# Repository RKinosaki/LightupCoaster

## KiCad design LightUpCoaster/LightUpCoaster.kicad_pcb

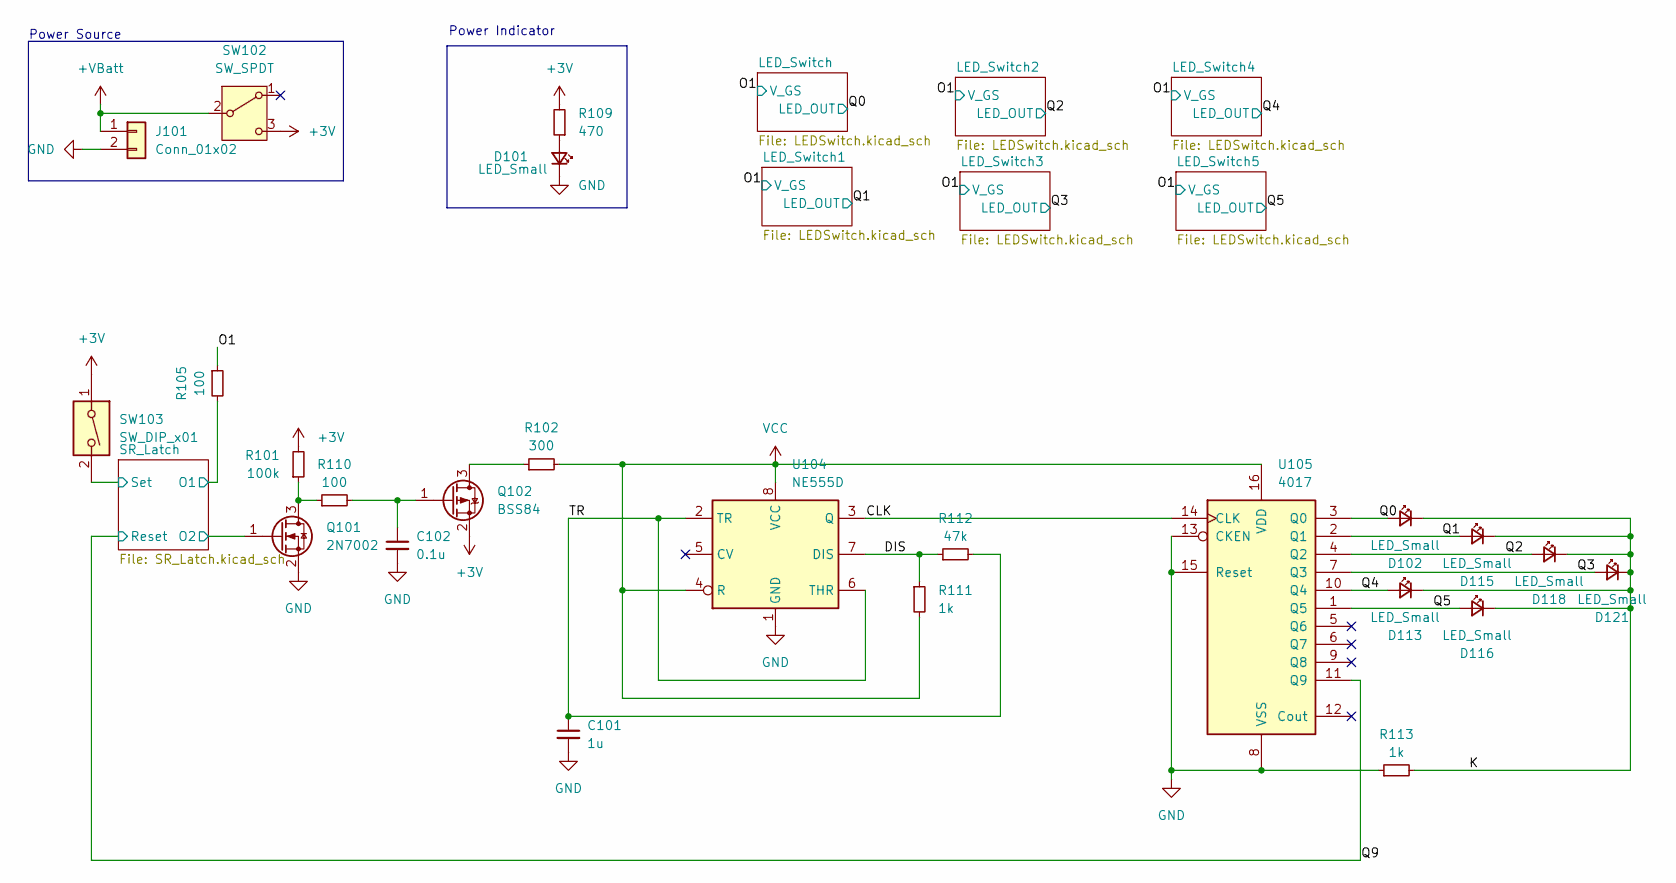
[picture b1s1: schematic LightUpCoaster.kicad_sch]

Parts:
C101: 1u; C_0402_1005Metric
C102: 0.1u; C_0402_1005Metric
D101, D102, D113, D115, D116, D118, D121: LED_Small; LED_0402_1005Metric
J101: Conn_01x02; PinHeader_1x02_P2.54mm_Vertical
Q101: 2N7002; SOT-23
Q102: BSS84; SOT-23
R101: 100k; R_0402_1005Metric
R102: 300; R_0402_1005Metric
R105, R110: 100; R_0402_1005Metric
R109: 470; R_0402_1005Metric
R111, R113: 1k; R_0402_1005Metric
R112: 47k; R_0402_1005Metric
SW102: SW_SPDT; PinHeader_1x03_P2.54mm_Vertical
SW103: SW_DIP_x01; SW_Push_1P1T_NO_E-Switch_TL3301NxxxxxG
U104: NE555D; SOIC-8_3.9x4.9mm_P1.27mm
U105: 4017; SOP-16_3.9x9.9mm_P1.27mm

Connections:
+3V: Q102.2 (S), R101.2, R109.2, SW102.3 (C), SW103.1; also elsewhere on the board
+VBatt: J101.1, SW102.2 (B)
/CLK: U104.3 (Q), U105.14 (CLK)
/DIS: R111.1, R112.1, U104.7 (DIS)
/K: D102.1 (K), D113.1 (K), D115.1 (K), D116.1 (K), D118.1 (K), D121.1 (K), R113.2
/O1: R105.1; also elsewhere on the board
/Q0: D102.2 (A), U105.3 (Q0); also elsewhere on the board
/Q1: D115.2 (A), U105.2 (Q1); also elsewhere on the board
/Q2: D118.2 (A), U105.4 (Q2); also elsewhere on the board
/Q3: D121.2 (A), U105.7 (Q3); also elsewhere on the board
/Q4: D113.2 (A), U105.10 (Q4); also elsewhere on the board
/Q5: D116.2 (A), U105.1 (Q5); also elsewhere on the board
/Q9: U105.11 (Q9); also elsewhere on the board
/SR_Latch/O1: R105.2; also elsewhere on the board
/SR_Latch/O2: Q101.1 (G); also elsewhere on the board
/SR_Latch/Set: SW103.2; also elsewhere on the board
/TR: C101.1, R112.2, U104.2 (TR), U104.6 (THR)
GND: C101.2, C102.2, D101.1 (K), J101.2, Q101.2 (S), R113.1, U104.1 (GND), U105.8 (VSS), U105.13 (CKEN), U105.15 (Reset); also elsewhere on the board
unnamed: D101.2 (A), R109.1
unnamed: Q101.3 (D), R101.1, R110.1
unnamed: Q102.3 (D), R102.1
unnamed: C102.1, Q102.1 (G), R110.2
VCC: R102.2, R111.2, U104.4 (R), U104.8 (VCC), U105.16 (VDD)

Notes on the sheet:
Power Source
Power Indicator

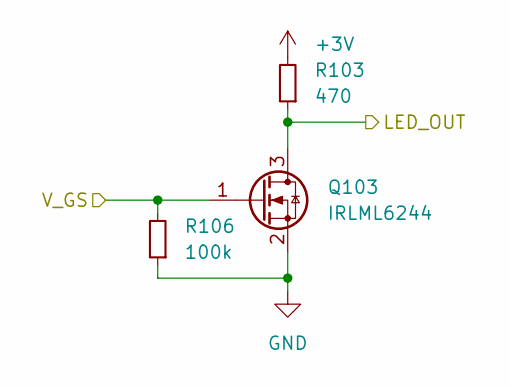
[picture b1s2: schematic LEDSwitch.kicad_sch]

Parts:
Q103: IRLML6244; SOT-23
R103: 470; R_0402_1005Metric
R106: 100k; R_0402_1005Metric

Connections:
+3V: R103.2; also elsewhere on the board
/O1: Q103.1 (G), R106.2; also elsewhere on the board
/Q0: Q103.3 (D), R103.1; also elsewhere on the board
GND: Q103.2 (S), R106.1; also elsewhere on the board

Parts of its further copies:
Q401, Q402, Q403, Q501, Q601: IRLML6244; SOT-23
R401, R403, R405, R501, R601: 100k; R_0402_1005Metric
R402, R404, R406, R502, R602: 470; R_0402_1005Metric

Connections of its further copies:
+3V: R402.2, R404.2, R406.2, R502.2, R602.2; also elsewhere on the board
/O1: Q401.1 (G), Q402.1 (G), Q403.1 (G), Q501.1 (G), Q601.1 (G), R401.2, R403.2, R405.2, R501.2, R601.2; also elsewhere on the board
/Q1: Q401.3 (D), R402.1; also elsewhere on the board
/Q2: Q403.3 (D), R406.1; also elsewhere on the board
/Q3: Q601.3 (D), R602.1; also elsewhere on the board
/Q4: Q402.3 (D), R404.1; also elsewhere on the board
/Q5: Q501.3 (D), R502.1; also elsewhere on the board
GND: Q401.2 (S), Q402.2 (S), Q403.2 (S), Q501.2 (S), Q601.2 (S), R401.1, R403.1, R405.1, R501.1, R601.1; also elsewhere on the board

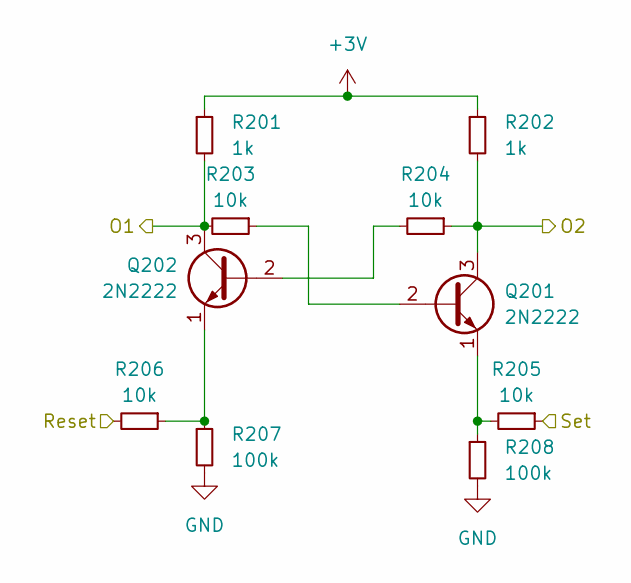
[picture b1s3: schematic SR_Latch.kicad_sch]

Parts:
Q201: 2N2222; TO-92
Q202: 2N2222; SOT-23
R201, R202: 1k; R_0402_1005Metric
R203, R204, R205, R206: 10k; R_0402_1005Metric
R207, R208: 100k; R_0402_1005Metric

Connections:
+3V: R201.1, R202.1; also elsewhere on the board
/Q9: R206.2; also elsewhere on the board
/SR_Latch/O1: Q202.3 (C), R201.2, R203.2; also elsewhere on the board
/SR_Latch/O2: Q201.3 (C), R202.2, R204.1; also elsewhere on the board
/SR_Latch/Set: R205.1; also elsewhere on the board
GND: R207.2, R208.2; also elsewhere on the board
unnamed: Q201.2 (B), R203.1
unnamed: Q201.1 (E), R205.2, R208.1
unnamed: Q202.2 (B), R204.2
unnamed: Q202.1 (E), R206.1, R207.1

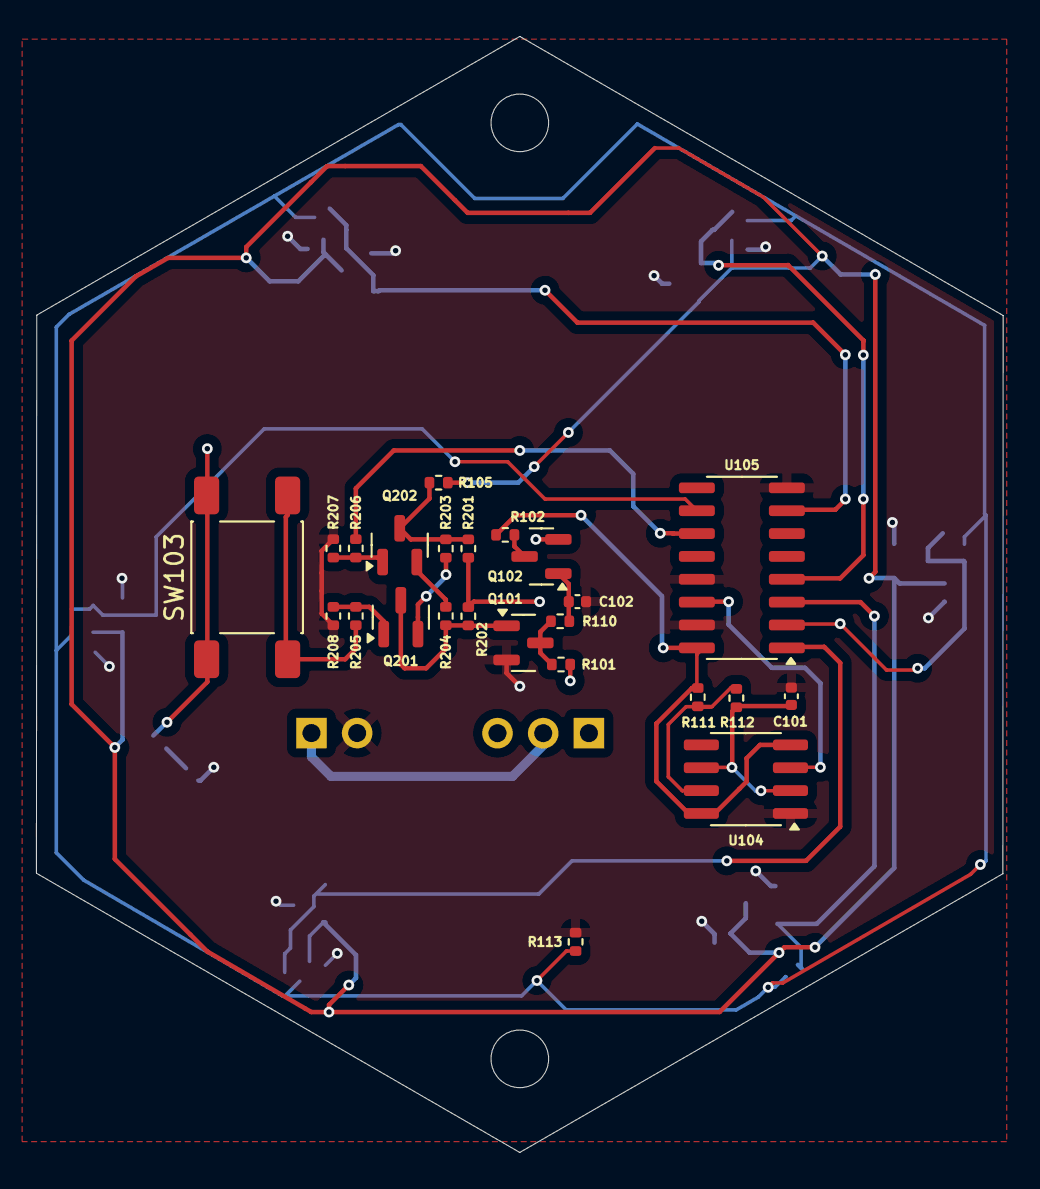
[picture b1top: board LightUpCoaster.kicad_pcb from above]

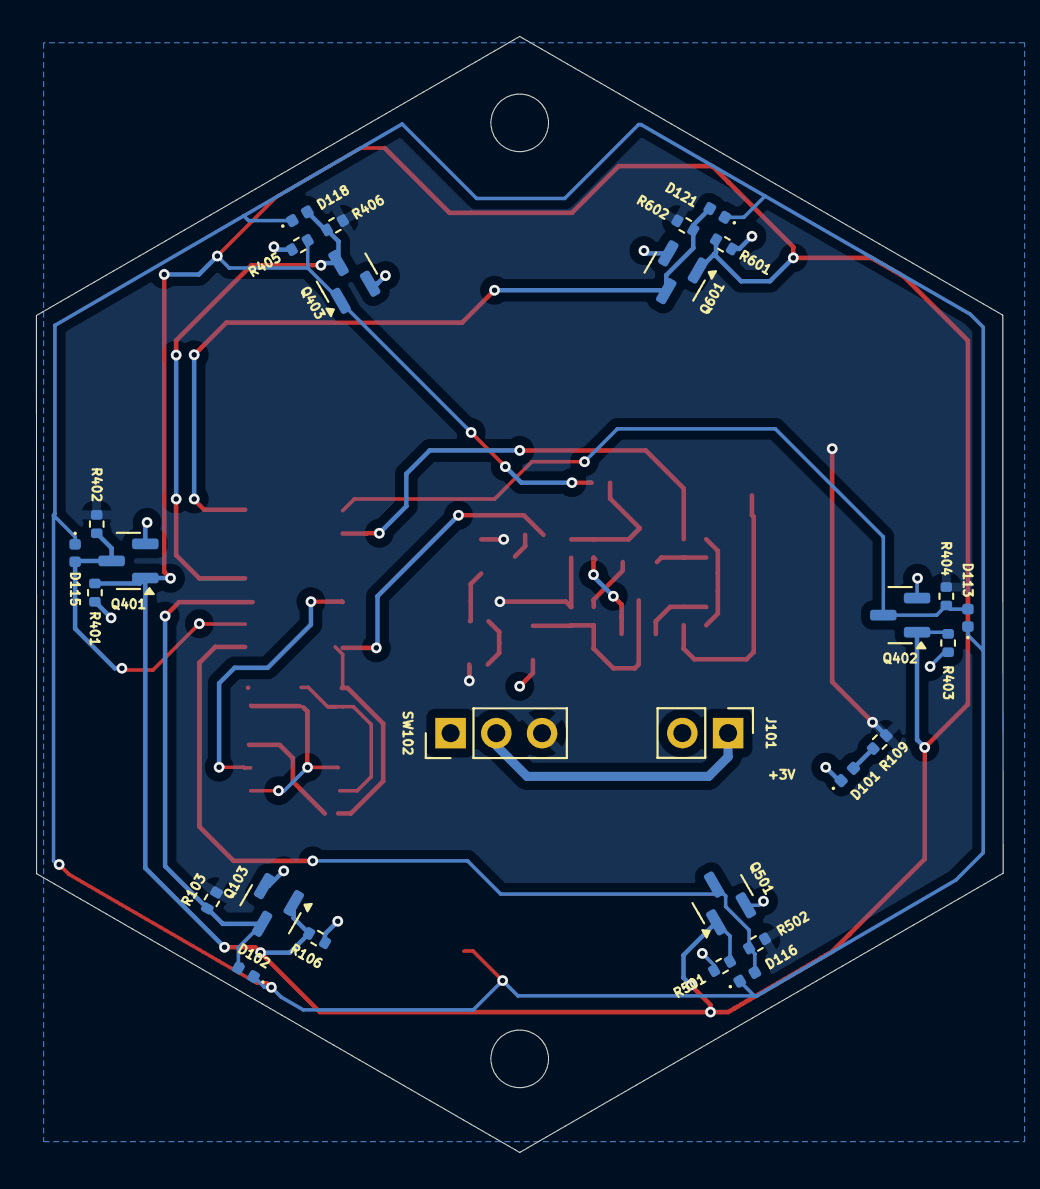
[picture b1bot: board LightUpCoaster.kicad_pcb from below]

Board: 2 copper layers, 53.7 x 62.0 mm, 52 parts (28 on the bottom side), 27 nets.

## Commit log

2025-09-06 PCB for lightupcoaster
2025-09-16 Fixed LED positions
